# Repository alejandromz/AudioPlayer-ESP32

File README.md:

# AudioPlayer-ESP32
Proyecto Sistemas Embebidos 2022-1. La documentación del proyecto se puede encontrar en el Wiki asociado a este repositorio. En la parte del código se pueden encontrar 3 carpetas: una con el desarrollo de la placa en Kikad, otra con el código de prueba de módulos individuales y la última con el código final del proyecto.

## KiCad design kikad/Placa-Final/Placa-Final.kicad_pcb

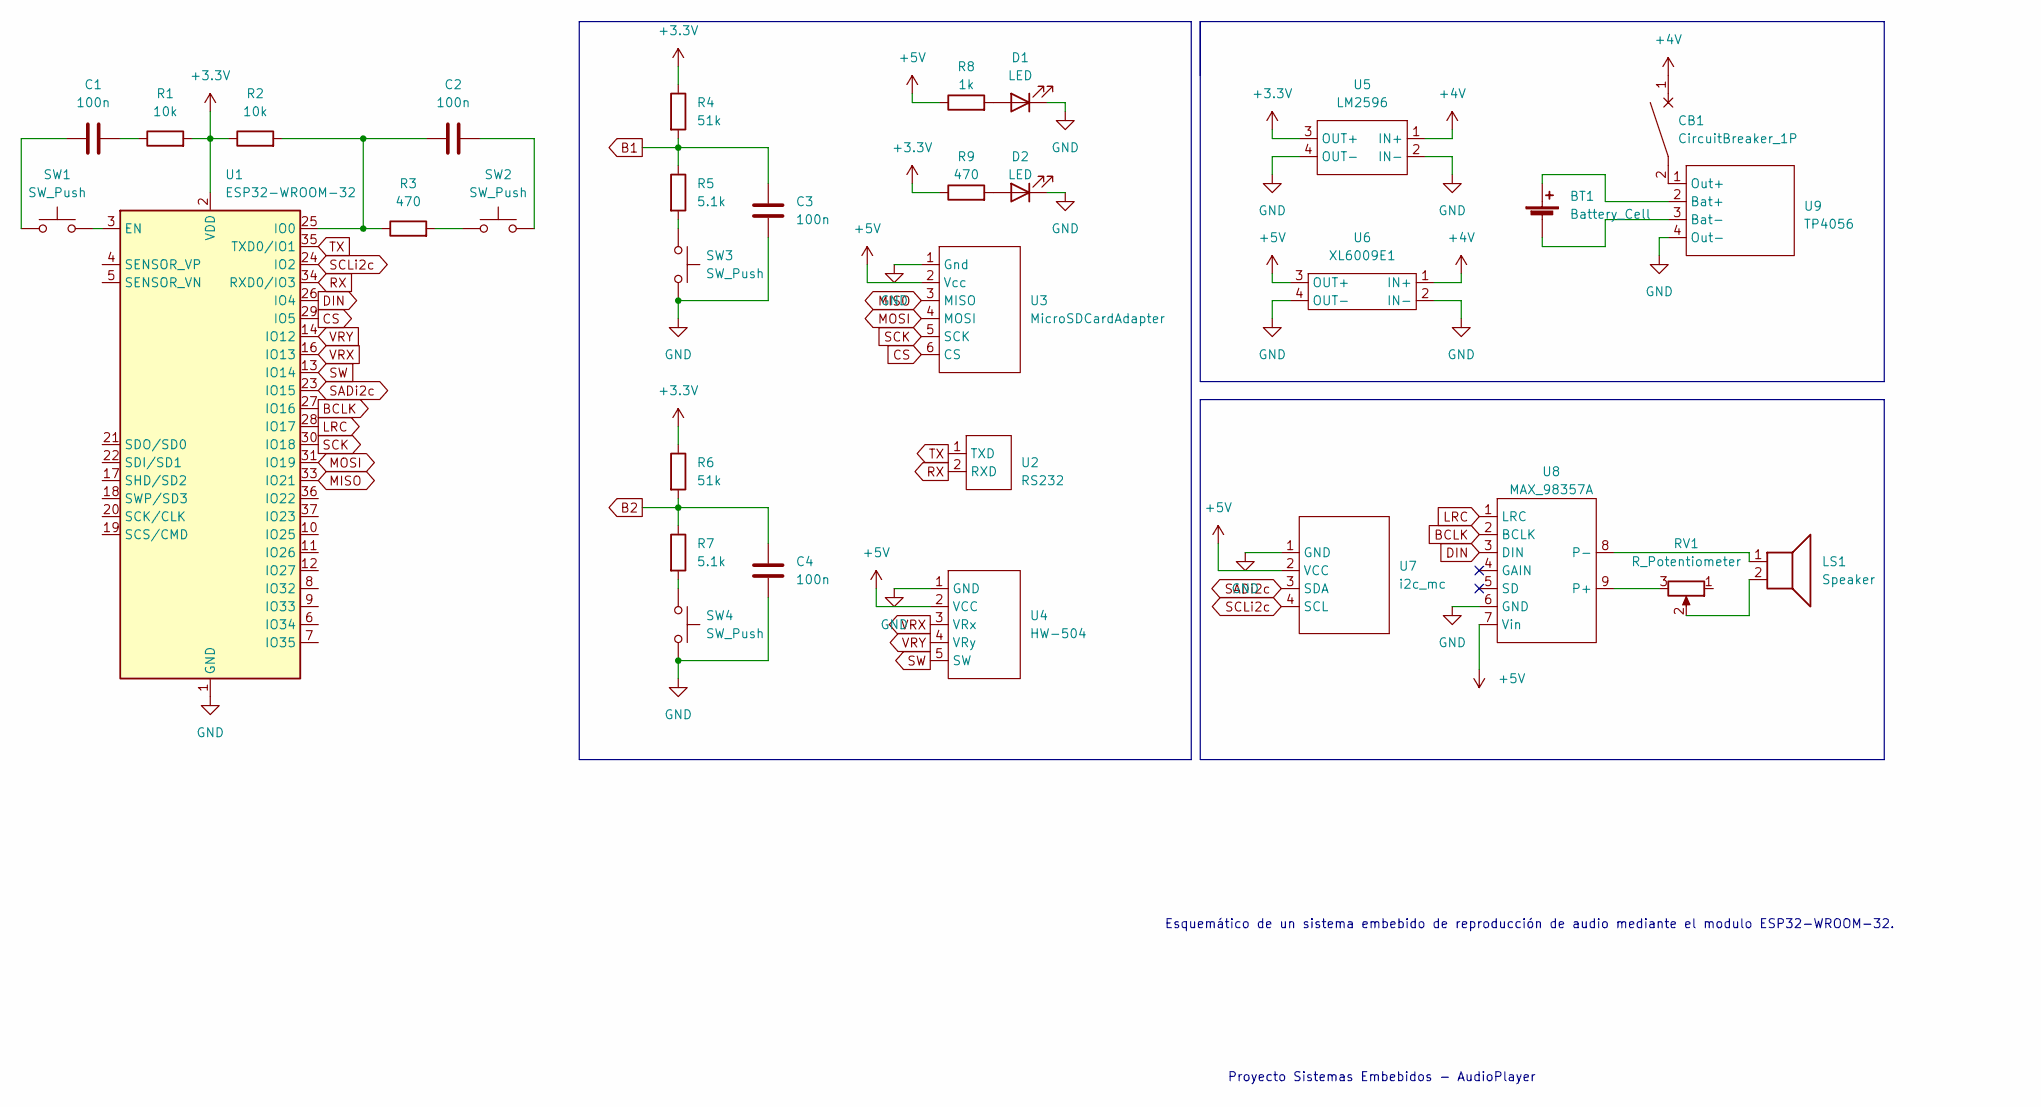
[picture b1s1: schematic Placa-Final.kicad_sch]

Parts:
BT1: Battery_Cell; PinHeader_1x02_P2.54mm_Vertical
C1, C2, C3, C4: 100n; C_0805_2012Metric_Pad1.18x1.45mm_HandSolder
CB1: CircuitBreaker_1P; SW_DIP_SPSTx01_Slide_9.78x4.72mm_W7.62mm_P2.54mm
D1, D2: LED; LED_D3.0mm
LS1: Speaker; PinHeader_1x02_P2.54mm_Vertical
R1, R2: 10k; R_0805_2012Metric_Pad1.20x1.40mm_HandSolder
R3, R9: 470; R_0805_2012Metric_Pad1.20x1.40mm_HandSolder
R4, R6: 51k; R_0805_2012Metric_Pad1.20x1.40mm_HandSolder
R5, R7: 5.1k; R_0805_2012Metric_Pad1.20x1.40mm_HandSolder
R8: 1k; R_0805_2012Metric_Pad1.20x1.40mm_HandSolder
RV1: R_Potentiometer; Potentiometer_Alps_RK09Y11_Single_Horizontal
SW1, SW2, SW3, SW4: SW_Push; SW_PUSH_6mm_H5mm
U1: ESP32-WROOM-32
U2: RS232; PinHeader_1x02_P2.54mm_Vertical
U3: MicroSDCardAdapter
U4: HW-504
U5: LM2596
U6: XL6009E1
U7: i2c_mc; PinHeader_1x04_P2.54mm_Vertical
U8: MAX_98357A; MAX98357a
U9: TP4056; Tp056

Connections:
+3V3: R1.2, R2.1, R4.1, R6.1, R9.1, U1.2 (VDD), U5.3 (OUT+)
+4V: CB1.1, U5.1 (IN+), U6.1 (IN+)
+5V: R8.1, U3.2 (Vcc), U4.2 (VCC), U6.3 (OUT+), U7.2 (VCC), U8.7 (Vin)
B1: C3.2, R4.2, R5.1
B2: C4.2, R6.2, R7.1
BCLK: U1.27 (IO16), U8.2 (BCLK)
CS: U1.29 (IO5), U3.6 (CS)
DIN: U1.26 (IO4), U8.3 (DIN)
GND: C3.1, C4.1, D1.1 (K), D2.1 (K), SW3.2, SW4.2, U1.1 (GND), U1.15 (GND), U1.38 (GND), U1.39 (GND), U3.1 (Gnd), U4.1 (GND), U5.2 (IN-), U5.4 (OUT-), U6.2 (IN-), U6.4 (OUT-), U7.1 (GND), U8.6 (GND), U9.4 (Out-)
LRC: U1.28 (IO17), U8.1 (LRC)
MISO: U1.33 (IO21), U3.3 (MISO)
MOSI: U1.31 (IO19), U3.4 (MOSI)
unnamed: BT1.1 (+), U9.2 (Bat+)
unnamed: BT1.2 (-), U9.3 (Bat-)
unnamed: C1.1, SW1.1
unnamed: C1.2, R1.1
unnamed: C2.1, R2.2, R3.1, U1.25 (IO0)
unnamed: C2.2, SW2.2
unnamed: CB1.2, U9.1 (Out+)
unnamed: D1.2 (A), R8.2
unnamed: D2.2 (A), R9.2
unnamed: LS1.1, U8.8 (P-)
unnamed: LS1.2, RV1.2
unnamed: R3.2, SW2.1
unnamed: R5.2, SW3.1
unnamed: R7.2, SW4.1
unnamed: RV1.3, U8.9 (P+)
unnamed: SW1.2, U1.3 (EN)
RX: U1.34 (RXD0/IO3), U2.2 (RXD)
SADi2c: U1.23 (IO15), U7.3 (SDA)
SCK: U1.30 (IO18), U3.5 (SCK)
SCLi2c: U1.24 (IO2), U7.4 (SCL)
SW: U1.13 (IO14), U4.5 (SW)
TX: U1.35 (TXD0/IO1), U2.1 (TXD)
VRX: U1.16 (IO13), U4.3 (VRx)
VRY: U1.14 (IO12), U4.4 (VRy)

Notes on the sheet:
Esquemático de un sistema embebido de reproducción de audio mediante el modulo ESP32-WROOM-32.
Proyecto Sistemas Embebidos - AudioPlayer

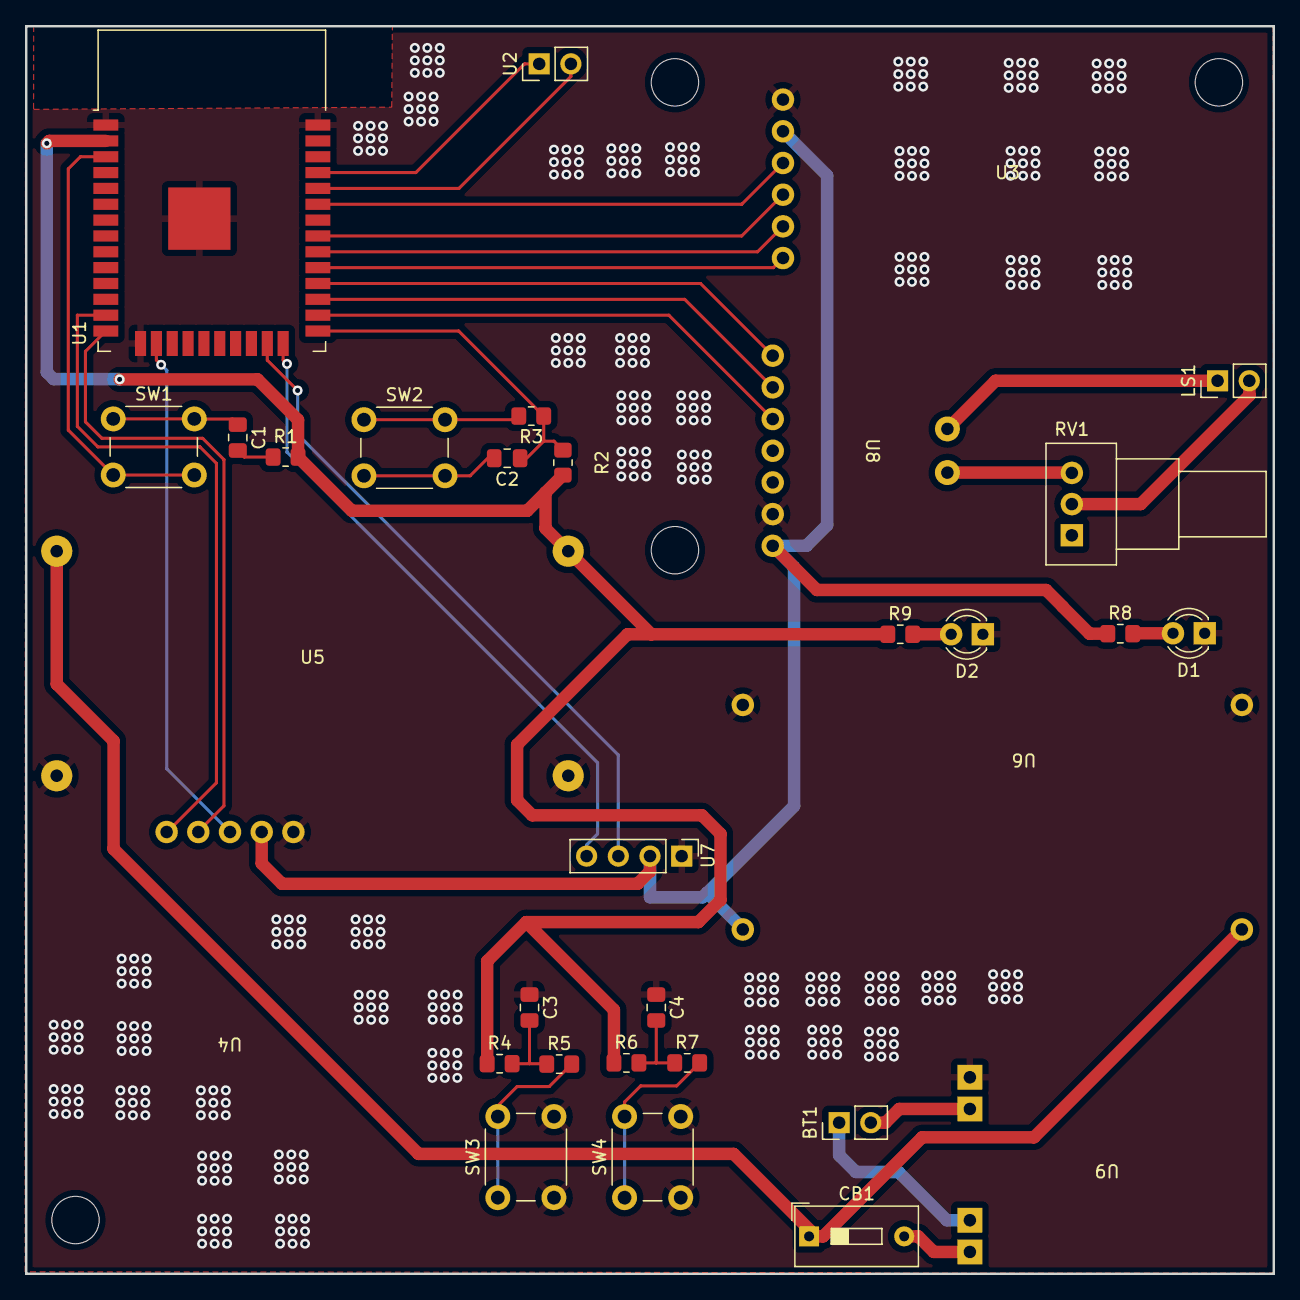
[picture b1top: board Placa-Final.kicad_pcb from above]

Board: 2 copper layers, 100.0 x 100.0 mm, 32 parts (0 on the bottom side), 36 nets.

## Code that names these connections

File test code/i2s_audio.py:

from machine import I2S
from machine import Pin
from time import sleep_ms


bck_pin = Pin(22)   # Pin BCLK
ws_pin = Pin(21)    # Pin LRC
sdout_pin = Pin(23) # Pin Din

audio_out = I2S(1,
                sck=bck_pin, ws=ws_pin, sd=sdout_pin,
                mode=I2S.TX, 
                bits=16, 
                format=I2S.MONO,
                rate=16000,
                ibuf=2000)
               
samples = bytearray([1,0,1,0,0,0,1,1,1,1,0,1,1,0]*100)

while True:
    num_bytes_written = audio_out.write(samples)
    sleep_ms(100)
